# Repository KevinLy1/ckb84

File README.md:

# CKB84
A DIY custom keyboard with 84 keys with per-key rgb and hotswappable keys.
Raspberry Pi RP2040 MCU.

## Features
- Hotswappable
- Per-key RGB Backlight
- 75% Layout
- QMK and Vial support
- 3D printed / CNC case and plate
- Custom layout : Backspace 2u, Left Shift 2u, Right Shift 2u, ISO Enter, Spacebar 6u

# Images

## Layout

## PCB

## Case and Plate

## Firmware

See [QMK Reproducible](https://github.com/KevinLy1/qmk_reproducible) -> diy/ckb84.

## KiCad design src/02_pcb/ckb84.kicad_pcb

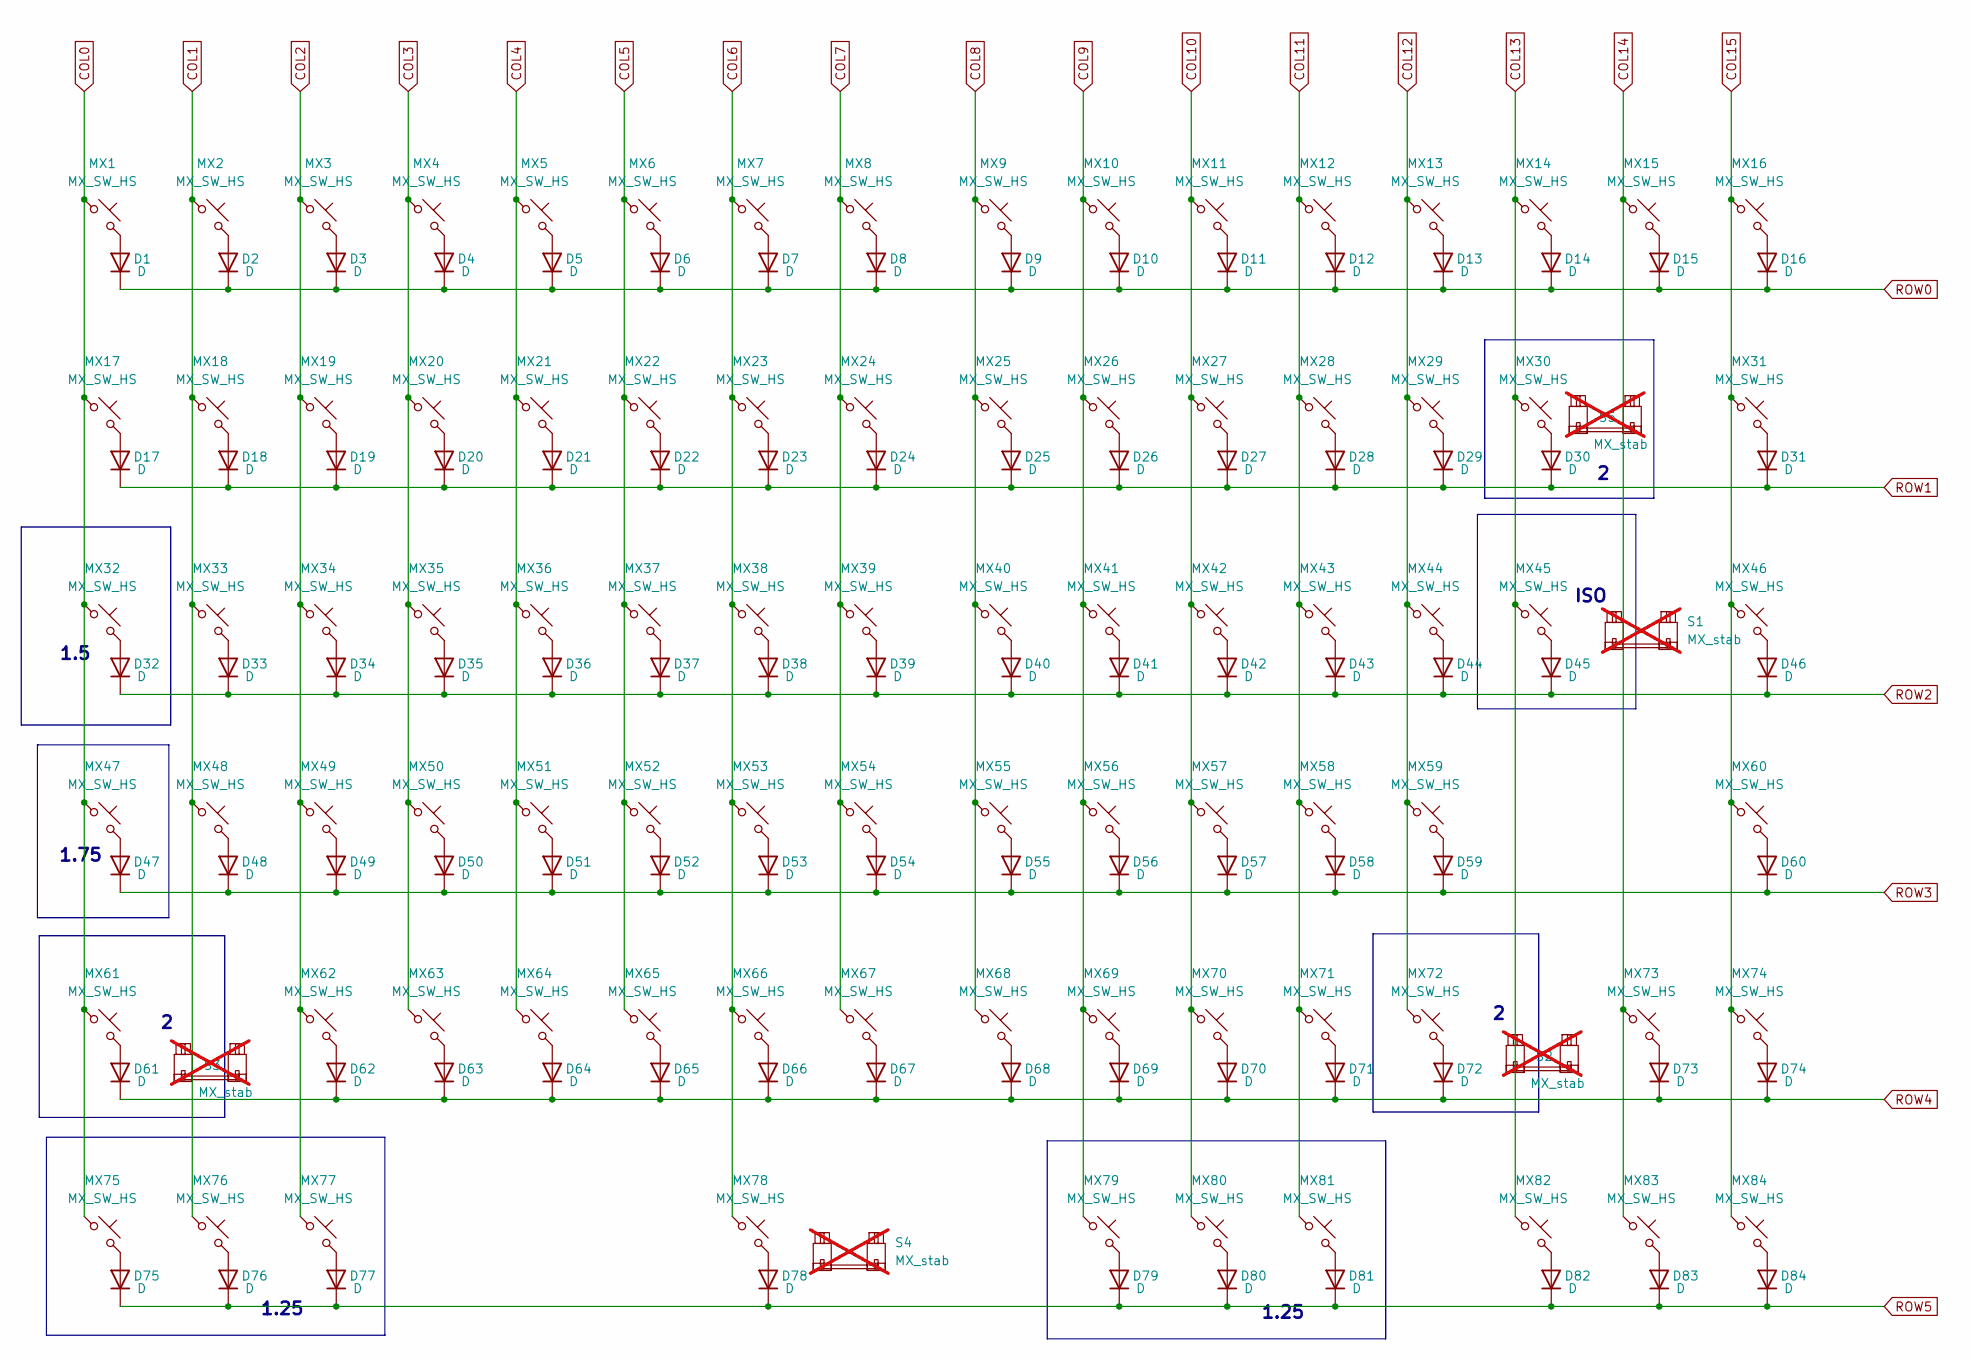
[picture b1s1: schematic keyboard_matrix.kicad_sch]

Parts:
D1, D2, D3, D4, D5, D6, D7, D8, D9, D10, D11, D12, D13, D14, D15, D16, D17, D18, D19, D20, D21, D22, D23, D24, D25, D26, D27, D28, D29, D30, D31, D32, D33, D34, D35, D36, D37, D38, D39, D40, D41, D42, D43, D44, D45, D46, D47, D48, D49, D50, D51, D52, D53, D54, D55, D56, D57, D58, D59, D60, D61, D62, D63, D64, D65, D66, D67, D68, D69, D70, D71, D72, D73, D74, D75, D76, D77, D78, D79, D80, D81, D82, D83, D84: D; D_SOD-123; MFR.Part # SOD1F7; LCSC C33221
MX1, MX2, MX3, MX4, MX5, MX6, MX7, MX8, MX9, MX10, MX11, MX12, MX13, MX14, MX15, MX16, MX17, MX18, MX19, MX20, MX21, MX22, MX23, MX24, MX25, MX26, MX27, MX28, MX29, MX30, MX31, MX33, MX34, MX35, MX36, MX37, MX38, MX39, MX40, MX41, MX42, MX43, MX44, MX45, MX46, MX48, MX49, MX50, MX51, MX52, MX53, MX54, MX55, MX56, MX57, MX58, MX59, MX60, MX61, MX62, MX63, MX64, MX65, MX66, MX67, MX68, MX69, MX70, MX71, MX72, MX73, MX74, MX76, MX78, MX80, MX82, MX83, MX84: MX_SW_HS; SW_MX_HS_CPG151101S11_1u; MFR.Part # CPG151101S11-16; LCSC C41430893
MX32: MX_SW_HS; SW_MX_HS_CPG151101S11_1.5u; MFR.Part # CPG151101S11-16; LCSC C41430893
MX47: MX_SW_HS; SW_MX_HS_CPG151101S11_1.75u; MFR.Part # CPG151101S11-16; LCSC C41430893
MX75, MX77, MX79, MX81: MX_SW_HS; SW_MX_HS_CPG151101S11_1.25u; MFR.Part # CPG151101S11-16; LCSC C41430893
S1: MX_stab; STAB_MX_ISO; MFR.Part # DNP; JLCPCB part# DNP; not fitted
S2, S3, S5: MX_stab; STAB_MX_P_2u; MFR.Part # DNP; JLCPCB part# DNP; not fitted
S4: MX_stab; STAB_MX_6u; MFR.Part # DNP; JLCPCB part# DNP; not fitted

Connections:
COL0: MX1.1, MX17.1, MX32.1, MX47.1, MX61.1, MX75.1; also elsewhere on the board
COL1: MX2.1, MX18.1, MX33.1, MX48.1, MX76.1; also elsewhere on the board
COL2: MX3.1, MX19.1, MX34.1, MX49.1, MX62.1, MX77.1; also elsewhere on the board
COL3: MX4.1, MX20.1, MX35.1, MX50.1, MX63.1; also elsewhere on the board
COL4: MX5.1, MX21.1, MX36.1, MX51.1, MX64.1; also elsewhere on the board
COL5: MX6.1, MX22.1, MX37.1, MX52.1, MX65.1; also elsewhere on the board
COL6: MX7.1, MX23.1, MX38.1, MX53.1, MX66.1, MX78.1; also elsewhere on the board
COL7: MX8.1, MX24.1, MX39.1, MX54.1, MX67.1; also elsewhere on the board
COL8: MX9.1, MX25.1, MX40.1, MX55.1, MX68.1; also elsewhere on the board
COL9: MX10.1, MX26.1, MX41.1, MX56.1, MX69.1, MX79.1; also elsewhere on the board
COL10: MX11.1, MX27.1, MX42.1, MX57.1, MX70.1, MX80.1; also elsewhere on the board
COL11: MX12.1, MX28.1, MX43.1, MX58.1, MX71.1, MX81.1; also elsewhere on the board
COL12: MX13.1, MX29.1, MX44.1, MX59.1, MX72.1; also elsewhere on the board
COL13: MX14.1, MX30.1, MX45.1, MX82.1; also elsewhere on the board
COL14: MX15.1, MX73.1, MX83.1; also elsewhere on the board
COL15: MX16.1, MX31.1, MX46.1, MX60.1, MX74.1, MX84.1; also elsewhere on the board
unnamed: D1.2 (A), MX1.2
unnamed: D2.2 (A), MX2.2
unnamed: D3.2 (A), MX3.2
unnamed: D4.2 (A), MX4.2
unnamed: D5.2 (A), MX5.2
unnamed: D6.2 (A), MX6.2
unnamed: D7.2 (A), MX7.2
unnamed: D8.2 (A), MX8.2
unnamed: D9.2 (A), MX9.2
unnamed: D10.2 (A), MX10.2
unnamed: D11.2 (A), MX11.2
unnamed: D12.2 (A), MX12.2
unnamed: D13.2 (A), MX13.2
unnamed: D14.2 (A), MX14.2
unnamed: D15.2 (A), MX15.2
unnamed: D16.2 (A), MX16.2
unnamed: D17.2 (A), MX17.2
unnamed: D18.2 (A), MX18.2
unnamed: D19.2 (A), MX19.2
unnamed: D20.2 (A), MX20.2
unnamed: D21.2 (A), MX21.2
unnamed: D22.2 (A), MX22.2
unnamed: D23.2 (A), MX23.2
unnamed: D24.2 (A), MX24.2
unnamed: D25.2 (A), MX25.2
unnamed: D26.2 (A), MX26.2
unnamed: D27.2 (A), MX27.2
unnamed: D28.2 (A), MX28.2
unnamed: D29.2 (A), MX29.2
unnamed: D30.2 (A), MX30.2
unnamed: D31.2 (A), MX31.2
unnamed: D32.2 (A), MX32.2
unnamed: D33.2 (A), MX33.2
unnamed: D34.2 (A), MX34.2
unnamed: D35.2 (A), MX35.2
unnamed: D36.2 (A), MX36.2
unnamed: D37.2 (A), MX37.2
unnamed: D38.2 (A), MX38.2
unnamed: D39.2 (A), MX39.2
unnamed: D40.2 (A), MX40.2
unnamed: D41.2 (A), MX41.2
unnamed: D42.2 (A), MX42.2
unnamed: D43.2 (A), MX43.2
unnamed: D44.2 (A), MX44.2
unnamed: D45.2 (A), MX45.2
unnamed: D46.2 (A), MX46.2
unnamed: D47.2 (A), MX47.2
unnamed: D48.2 (A), MX48.2
unnamed: D49.2 (A), MX49.2
unnamed: D50.2 (A), MX50.2
unnamed: D51.2 (A), MX51.2
unnamed: D52.2 (A), MX52.2
unnamed: D53.2 (A), MX53.2
unnamed: D54.2 (A), MX54.2
unnamed: D55.2 (A), MX55.2
unnamed: D56.2 (A), MX56.2
unnamed: D57.2 (A), MX57.2
unnamed: D58.2 (A), MX58.2
unnamed: D59.2 (A), MX59.2
unnamed: D60.2 (A), MX60.2
unnamed: D61.2 (A), MX61.2
unnamed: D62.2 (A), MX62.2
unnamed: D63.2 (A), MX63.2
unnamed: D64.2 (A), MX64.2
unnamed: D65.2 (A), MX65.2
unnamed: D66.2 (A), MX66.2
unnamed: D67.2 (A), MX67.2
unnamed: D68.2 (A), MX68.2
unnamed: D69.2 (A), MX69.2
unnamed: D70.2 (A), MX70.2
unnamed: D71.2 (A), MX71.2
unnamed: D72.2 (A), MX72.2
unnamed: D73.2 (A), MX73.2
unnamed: D74.2 (A), MX74.2
unnamed: D75.2 (A), MX75.2
unnamed: D76.2 (A), MX76.2
unnamed: D77.2 (A), MX77.2
unnamed: D78.2 (A), MX78.2
unnamed: D79.2 (A), MX79.2
unnamed: D80.2 (A), MX80.2
unnamed: D81.2 (A), MX81.2
unnamed: D82.2 (A), MX82.2
unnamed: D83.2 (A), MX83.2
unnamed: D84.2 (A), MX84.2
ROW0: D1.1 (K), D2.1 (K), D3.1 (K), D4.1 (K), D5.1 (K), D6.1 (K), D7.1 (K), D8.1 (K), D9.1 (K), D10.1 (K), D11.1 (K), D12.1 (K), D13.1 (K), D14.1 (K), D15.1 (K), D16.1 (K); also elsewhere on the board
ROW1: D17.1 (K), D18.1 (K), D19.1 (K), D20.1 (K), D21.1 (K), D22.1 (K), D23.1 (K), D24.1 (K), D25.1 (K), D26.1 (K), D27.1 (K), D28.1 (K), D29.1 (K), D30.1 (K), D31.1 (K); also elsewhere on the board
ROW2: D32.1 (K), D33.1 (K), D34.1 (K), D35.1 (K), D36.1 (K), D37.1 (K), D38.1 (K), D39.1 (K), D40.1 (K), D41.1 (K), D42.1 (K), D43.1 (K), D44.1 (K), D45.1 (K), D46.1 (K); also elsewhere on the board
ROW3: D47.1 (K), D48.1 (K), D49.1 (K), D50.1 (K), D51.1 (K), D52.1 (K), D53.1 (K), D54.1 (K), D55.1 (K), D56.1 (K), D57.1 (K), D58.1 (K), D59.1 (K), D60.1 (K); also elsewhere on the board
ROW4: D61.1 (K), D62.1 (K), D63.1 (K), D64.1 (K), D65.1 (K), D66.1 (K), D67.1 (K), D68.1 (K), D69.1 (K), D70.1 (K), D71.1 (K), D72.1 (K), D73.1 (K), D74.1 (K); also elsewhere on the board
ROW5: D75.1 (K), D76.1 (K), D77.1 (K), D78.1 (K), D79.1 (K), D80.1 (K), D81.1 (K), D82.1 (K), D83.1 (K), D84.1 (K); also elsewhere on the board

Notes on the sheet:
ISO
1.75
1.25
1.5

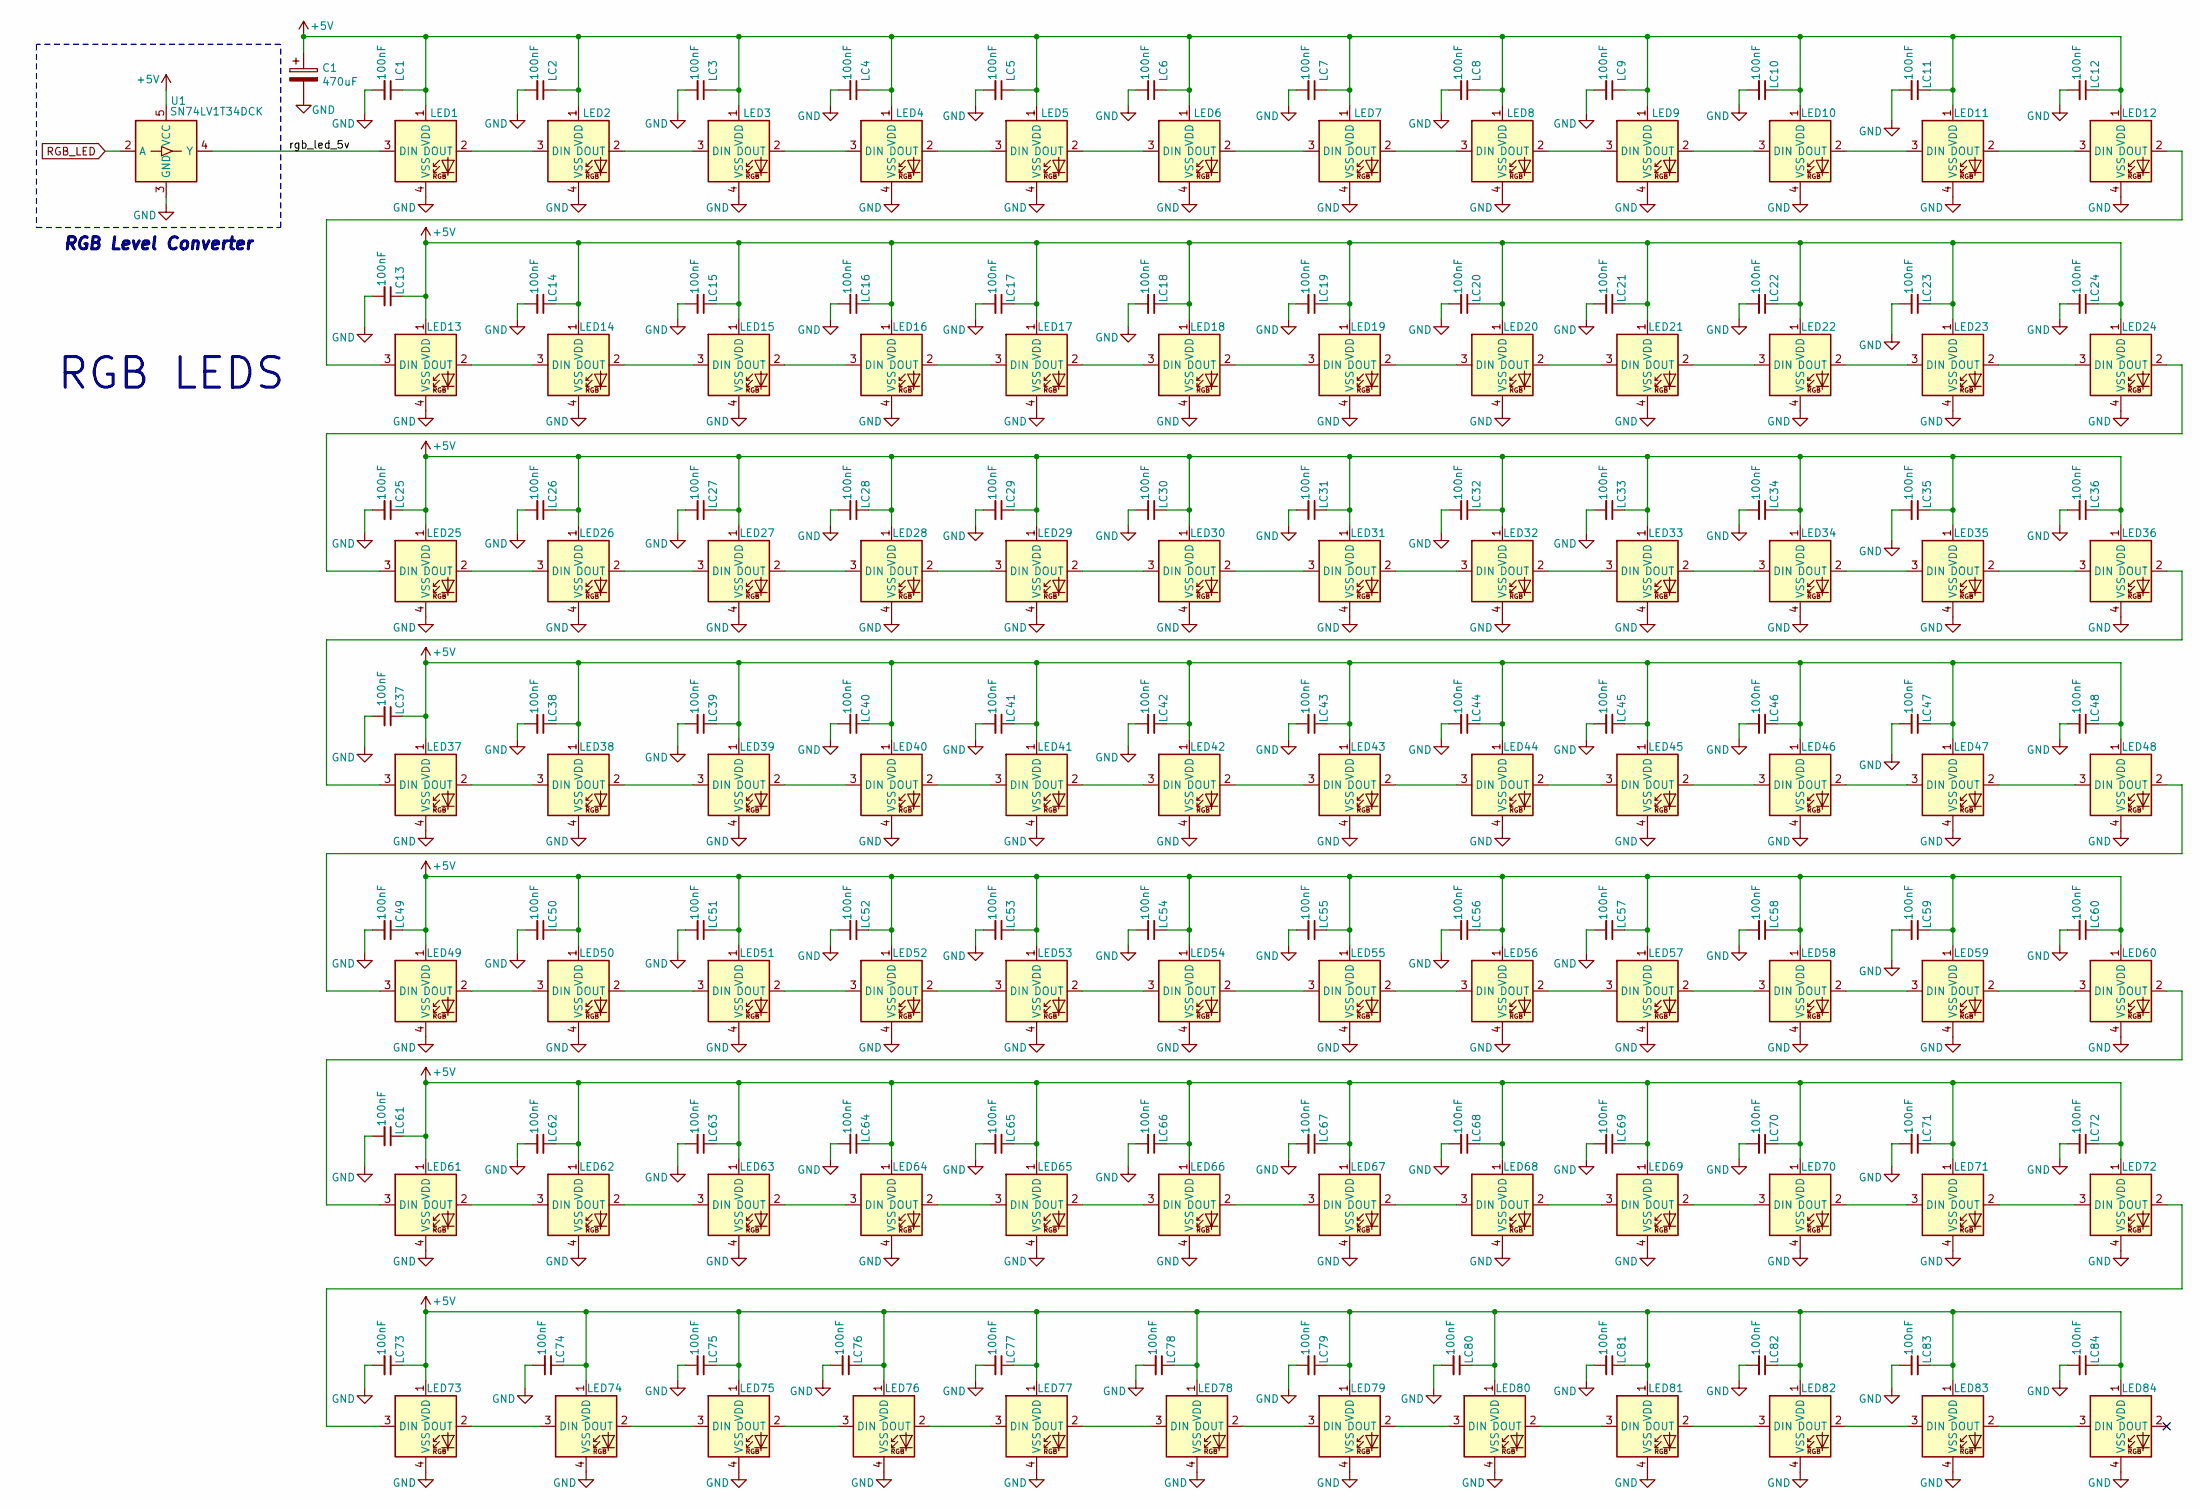
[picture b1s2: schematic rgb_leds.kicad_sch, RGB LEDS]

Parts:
C1: 470uF; CP_EIA-7343-31_Kemet-D; MFR.Part # TAJD477K006RNJ; JLCPCB Part # C7229
LC1, LC2, LC3, LC4, LC5, LC6, LC7, LC8, LC9, LC10, LC11, LC12, LC13, LC14, LC15, LC16, LC17, LC18, LC19, LC20, LC21, LC22, LC23, LC24, LC25, LC26, LC27, LC28, LC29, LC30, LC31, LC32, LC33, LC34, LC35, LC36, LC37, LC38, LC39, LC40, LC41, LC42, LC43, LC44, LC45, LC46, LC47, LC48, LC49, LC50, LC51, LC52, LC53, LC54, LC55, LC56, LC57, LC58, LC59, LC60, LC61, LC62, LC63, LC64, LC65, LC66, LC67, LC68, LC69, LC70, LC71, LC72, LC73, LC74, LC75, LC76, LC77, LC78, LC79, LC80, LC81, LC82, LC83, LC84: 100nF; C_0402_1005Metric; LCSC C1525
LED1, LED2, LED3, LED4, LED5, LED6, LED7, LED8, LED9, LED10, LED11, LED12, LED13, LED14, LED15, LED16, LED17, LED18, LED19, LED20, LED21, LED22, LED23, LED24, LED25, LED26, LED27, LED28, LED29, LED30, LED31, LED32, LED33, LED34, LED35, LED36, LED37, LED38, LED39, LED40, LED41, LED42, LED43, LED44, LED45, LED46, LED47, LED48, LED49, LED50, LED51, LED52, LED53, LED54, LED55, LED56, LED57, LED58, LED59, LED60, LED61, LED62, LED63, LED64, LED65, LED66, LED67, LED68, LED69, LED70, LED71, LED72, LED73, LED74, LED75, LED76, LED77, LED78, LED79, LED80, LED81, LED82, LED83, LED84: MX_SK6812MINI-E; LED_MX_6028R; LCSC C5149201
U1: SN74LV1T34DCK; SOT-353_SC-70-5; LCSC C48543212

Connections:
+5V: C1.1, LC1.1, LC2.1, LC3.1, LC4.1, LC5.1, LC6.1, LC7.1, LC8.1, LC9.1, LC10.1, LC11.1, LC12.1, LC13.1, LC14.1, LC15.1, LC16.1, LC17.1, LC18.1, LC19.1, LC20.1, LC21.1, LC22.1, LC23.1, LC24.1, LC25.1, LC26.1, LC27.1, LC28.1, LC29.1, LC30.1, LC31.1, LC32.1, LC33.1, LC34.1, LC35.1, LC36.1, LC37.1, LC38.1, LC39.1, LC40.1, LC41.1, LC42.1, LC43.1, LC44.1, LC45.1, LC46.1, LC47.1, LC48.1, LC49.1, LC50.1, LC51.1, LC52.1, LC53.1, LC54.1, LC55.1, LC56.1, LC57.1, LC58.1, LC59.1, LC60.1, LC61.1, LC62.1, LC63.1, LC64.1, LC65.1, LC66.1, LC67.1, LC68.1, LC69.1, LC70.1, LC71.1, LC72.1, LC73.1, LC74.1, LC75.1, LC76.1, LC77.1, LC78.1, LC79.1, LC80.1, LC81.1, LC82.1, LC83.1, LC84.1, LED1.1 (VDD), LED2.1 (VDD), LED3.1 (VDD), LED4.1 (VDD), LED5.1 (VDD), LED6.1 (VDD), LED7.1 (VDD), LED8.1 (VDD), LED9.1 (VDD), LED10.1 (VDD), LED11.1 (VDD), LED12.1 (VDD), LED13.1 (VDD), LED14.1 (VDD), LED15.1 (VDD), LED16.1 (VDD), LED17.1 (VDD), LED18.1 (VDD), LED19.1 (VDD), LED20.1 (VDD), LED21.1 (VDD), LED22.1 (VDD), LED23.1 (VDD), LED24.1 (VDD), LED25.1 (VDD), LED26.1 (VDD), LED27.1 (VDD), LED28.1 (VDD), LED29.1 (VDD), LED30.1 (VDD), LED31.1 (VDD), LED32.1 (VDD), LED33.1 (VDD), LED34.1 (VDD), LED35.1 (VDD), LED36.1 (VDD), LED37.1 (VDD), LED38.1 (VDD), LED39.1 (VDD), LED40.1 (VDD), LED41.1 (VDD), LED42.1 (VDD), LED43.1 (VDD), LED44.1 (VDD), LED45.1 (VDD), LED46.1 (VDD), LED47.1 (VDD), LED48.1 (VDD), LED49.1 (VDD), LED50.1 (VDD), LED51.1 (VDD), LED52.1 (VDD), LED53.1 (VDD), LED54.1 (VDD), LED55.1 (VDD), LED56.1 (VDD), LED57.1 (VDD), LED58.1 (VDD), LED59.1 (VDD), LED60.1 (VDD), LED61.1 (VDD), LED62.1 (VDD), LED63.1 (VDD), LED64.1 (VDD), LED65.1 (VDD), LED66.1 (VDD), LED67.1 (VDD), LED68.1 (VDD), LED69.1 (VDD), LED70.1 (VDD), LED71.1 (VDD), LED72.1 (VDD), LED73.1 (VDD), LED74.1 (VDD), LED75.1 (VDD), LED76.1 (VDD), LED77.1 (VDD), LED78.1 (VDD), LED79.1 (VDD), LED80.1 (VDD), LED81.1 (VDD), LED82.1 (VDD), LED83.1 (VDD), LED84.1 (VDD), U1.5 (VCC); also elsewhere on the board
/RGB LEDs/rgb_led_5v: LED1.3 (DIN), U1.4 (Y)
GND: C1.2, LC1.2, LC2.2, LC3.2, LC4.2, LC5.2, LC6.2, LC7.2, LC8.2, LC9.2, LC10.2, LC11.2, LC12.2, LC13.2, LC14.2, LC15.2, LC16.2, LC17.2, LC18.2, LC19.2, LC20.2, LC21.2, LC22.2, LC23.2, LC24.2, LC25.2, LC26.2, LC27.2, LC28.2, LC29.2, LC30.2, LC31.2, LC32.2, LC33.2, LC34.2, LC35.2, LC36.2, LC37.2, LC38.2, LC39.2, LC40.2, LC41.2, LC42.2, LC43.2, LC44.2, LC45.2, LC46.2, LC47.2, LC48.2, LC49.2, LC50.2, LC51.2, LC52.2, LC53.2, LC54.2, LC55.2, LC56.2, LC57.2, LC58.2, LC59.2, LC60.2, LC61.2, LC62.2, LC63.2, LC64.2, LC65.2, LC66.2, LC67.2, LC68.2, LC69.2, LC70.2, LC71.2, LC72.2, LC73.2, LC74.2, LC75.2, LC76.2, LC77.2, LC78.2, LC79.2, LC80.2, LC81.2, LC82.2, LC83.2, LC84.2, LED1.4 (VSS), LED2.4 (VSS), LED3.4 (VSS), LED4.4 (VSS), LED5.4 (VSS), LED6.4 (VSS), LED7.4 (VSS), LED8.4 (VSS), LED9.4 (VSS), LED10.4 (VSS), LED11.4 (VSS), LED12.4 (VSS), LED13.4 (VSS), LED14.4 (VSS), LED15.4 (VSS), LED16.4 (VSS), LED17.4 (VSS), LED18.4 (VSS), LED19.4 (VSS), LED20.4 (VSS), LED21.4 (VSS), LED22.4 (VSS), LED23.4 (VSS), LED24.4 (VSS), LED25.4 (VSS), LED26.4 (VSS), LED27.4 (VSS), LED28.4 (VSS), LED29.4 (VSS), LED30.4 (VSS), LED31.4 (VSS), LED32.4 (VSS), LED33.4 (VSS), LED34.4 (VSS), LED35.4 (VSS), LED36.4 (VSS), LED37.4 (VSS), LED38.4 (VSS), LED39.4 (VSS), LED40.4 (VSS), LED41.4 (VSS), LED42.4 (VSS), LED43.4 (VSS), LED44.4 (VSS), LED45.4 (VSS), LED46.4 (VSS), LED47.4 (VSS), LED48.4 (VSS), LED49.4 (VSS), LED50.4 (VSS), LED51.4 (VSS), LED52.4 (VSS), LED53.4 (VSS), LED54.4 (VSS), LED55.4 (VSS), LED56.4 (VSS), LED57.4 (VSS), LED58.4 (VSS), LED59.4 (VSS), LED60.4 (VSS), LED61.4 (VSS), LED62.4 (VSS), LED63.4 (VSS), LED64.4 (VSS), LED65.4 (VSS), LED66.4 (VSS), LED67.4 (VSS), LED68.4 (VSS), LED69.4 (VSS), LED70.4 (VSS), LED71.4 (VSS), LED72.4 (VSS), LED73.4 (VSS), LED74.4 (VSS), LED75.4 (VSS), LED76.4 (VSS), LED77.4 (VSS), LED78.4 (VSS), LED79.4 (VSS), LED80.4 (VSS), LED81.4 (VSS), LED82.4 (VSS), LED83.4 (VSS), LED84.4 (VSS), U1.3 (GND); also elsewhere on the board
unnamed: LED1.2 (DOUT), LED2.3 (DIN)
unnamed: LED2.2 (DOUT), LED3.3 (DIN)
unnamed: LED3.2 (DOUT), LED4.3 (DIN)
unnamed: LED4.2 (DOUT), LED5.3 (DIN)
unnamed: LED5.2 (DOUT), LED6.3 (DIN)
unnamed: LED6.2 (DOUT), LED7.3 (DIN)
unnamed: LED7.2 (DOUT), LED8.3 (DIN)
unnamed: LED8.2 (DOUT), LED9.3 (DIN)
unnamed: LED9.2 (DOUT), LED10.3 (DIN)
unnamed: LED10.2 (DOUT), LED11.3 (DIN)
unnamed: LED11.2 (DOUT), LED12.3 (DIN)
unnamed: LED12.2 (DOUT), LED13.3 (DIN)
unnamed: LED13.2 (DOUT), LED14.3 (DIN)
unnamed: LED14.2 (DOUT), LED15.3 (DIN)
unnamed: LED15.2 (DOUT), LED16.3 (DIN)
unnamed: LED16.2 (DOUT), LED17.3 (DIN)
unnamed: LED17.2 (DOUT), LED18.3 (DIN)
unnamed: LED18.2 (DOUT), LED19.3 (DIN)
unnamed: LED19.2 (DOUT), LED20.3 (DIN)
unnamed: LED20.2 (DOUT), LED21.3 (DIN)
unnamed: LED21.2 (DOUT), LED22.3 (DIN)
unnamed: LED22.2 (DOUT), LED23.3 (DIN)
unnamed: LED23.2 (DOUT), LED24.3 (DIN)
unnamed: LED24.2 (DOUT), LED25.3 (DIN)
unnamed: LED25.2 (DOUT), LED26.3 (DIN)
unnamed: LED26.2 (DOUT), LED27.3 (DIN)
unnamed: LED27.2 (DOUT), LED28.3 (DIN)
unnamed: LED28.2 (DOUT), LED29.3 (DIN)
unnamed: LED29.2 (DOUT), LED30.3 (DIN)
unnamed: LED30.2 (DOUT), LED31.3 (DIN)
unnamed: LED31.2 (DOUT), LED32.3 (DIN)
unnamed: LED32.2 (DOUT), LED33.3 (DIN)
unnamed: LED33.2 (DOUT), LED34.3 (DIN)
unnamed: LED34.2 (DOUT), LED35.3 (DIN)
unnamed: LED35.2 (DOUT), LED36.3 (DIN)
unnamed: LED36.2 (DOUT), LED37.3 (DIN)
unnamed: LED37.2 (DOUT), LED38.3 (DIN)
unnamed: LED38.2 (DOUT), LED39.3 (DIN)
unnamed: LED39.2 (DOUT), LED40.3 (DIN)
unnamed: LED40.2 (DOUT), LED41.3 (DIN)
unnamed: LED41.2 (DOUT), LED42.3 (DIN)
unnamed: LED42.2 (DOUT), LED43.3 (DIN)
unnamed: LED43.2 (DOUT), LED44.3 (DIN)
unnamed: LED44.2 (DOUT), LED45.3 (DIN)
unnamed: LED45.2 (DOUT), LED46.3 (DIN)
unnamed: LED46.2 (DOUT), LED47.3 (DIN)
unnamed: LED47.2 (DOUT), LED48.3 (DIN)
unnamed: LED48.2 (DOUT), LED49.3 (DIN)
unnamed: LED49.2 (DOUT), LED50.3 (DIN)
unnamed: LED50.2 (DOUT), LED51.3 (DIN)
unnamed: LED51.2 (DOUT), LED52.3 (DIN)
unnamed: LED52.2 (DOUT), LED53.3 (DIN)
unnamed: LED53.2 (DOUT), LED54.3 (DIN)
unnamed: LED54.2 (DOUT), LED55.3 (DIN)
unnamed: LED55.2 (DOUT), LED56.3 (DIN)
unnamed: LED56.2 (DOUT), LED57.3 (DIN)
unnamed: LED57.2 (DOUT), LED58.3 (DIN)
unnamed: LED58.2 (DOUT), LED59.3 (DIN)
unnamed: LED59.2 (DOUT), LED60.3 (DIN)
unnamed: LED60.2 (DOUT), LED61.3 (DIN)
unnamed: LED61.2 (DOUT), LED62.3 (DIN)
unnamed: LED62.2 (DOUT), LED63.3 (DIN)
unnamed: LED63.2 (DOUT), LED64.3 (DIN)
unnamed: LED64.2 (DOUT), LED65.3 (DIN)
unnamed: LED65.2 (DOUT), LED66.3 (DIN)
unnamed: LED66.2 (DOUT), LED67.3 (DIN)
unnamed: LED67.2 (DOUT), LED68.3 (DIN)
unnamed: LED68.2 (DOUT), LED69.3 (DIN)
unnamed: LED69.2 (DOUT), LED70.3 (DIN)
unnamed: LED70.2 (DOUT), LED71.3 (DIN)
unnamed: LED71.2 (DOUT), LED72.3 (DIN)
unnamed: LED72.2 (DOUT), LED73.3 (DIN)
unnamed: LED73.2 (DOUT), LED74.3 (DIN)
unnamed: LED74.2 (DOUT), LED75.3 (DIN)
unnamed: LED75.2 (DOUT), LED76.3 (DIN)
unnamed: LED76.2 (DOUT), LED77.3 (DIN)
unnamed: LED77.2 (DOUT), LED78.3 (DIN)
unnamed: LED78.2 (DOUT), LED79.3 (DIN)
unnamed: LED79.2 (DOUT), LED80.3 (DIN)
unnamed: LED80.2 (DOUT), LED81.3 (DIN)
unnamed: LED81.2 (DOUT), LED82.3 (DIN)
unnamed: LED82.2 (DOUT), LED83.3 (DIN)
unnamed: LED83.2 (DOUT), LED84.3 (DIN)
RGB_LED: U1.2 (A); also elsewhere on the board

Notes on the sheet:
RGB Level Converter
RGB LEDS

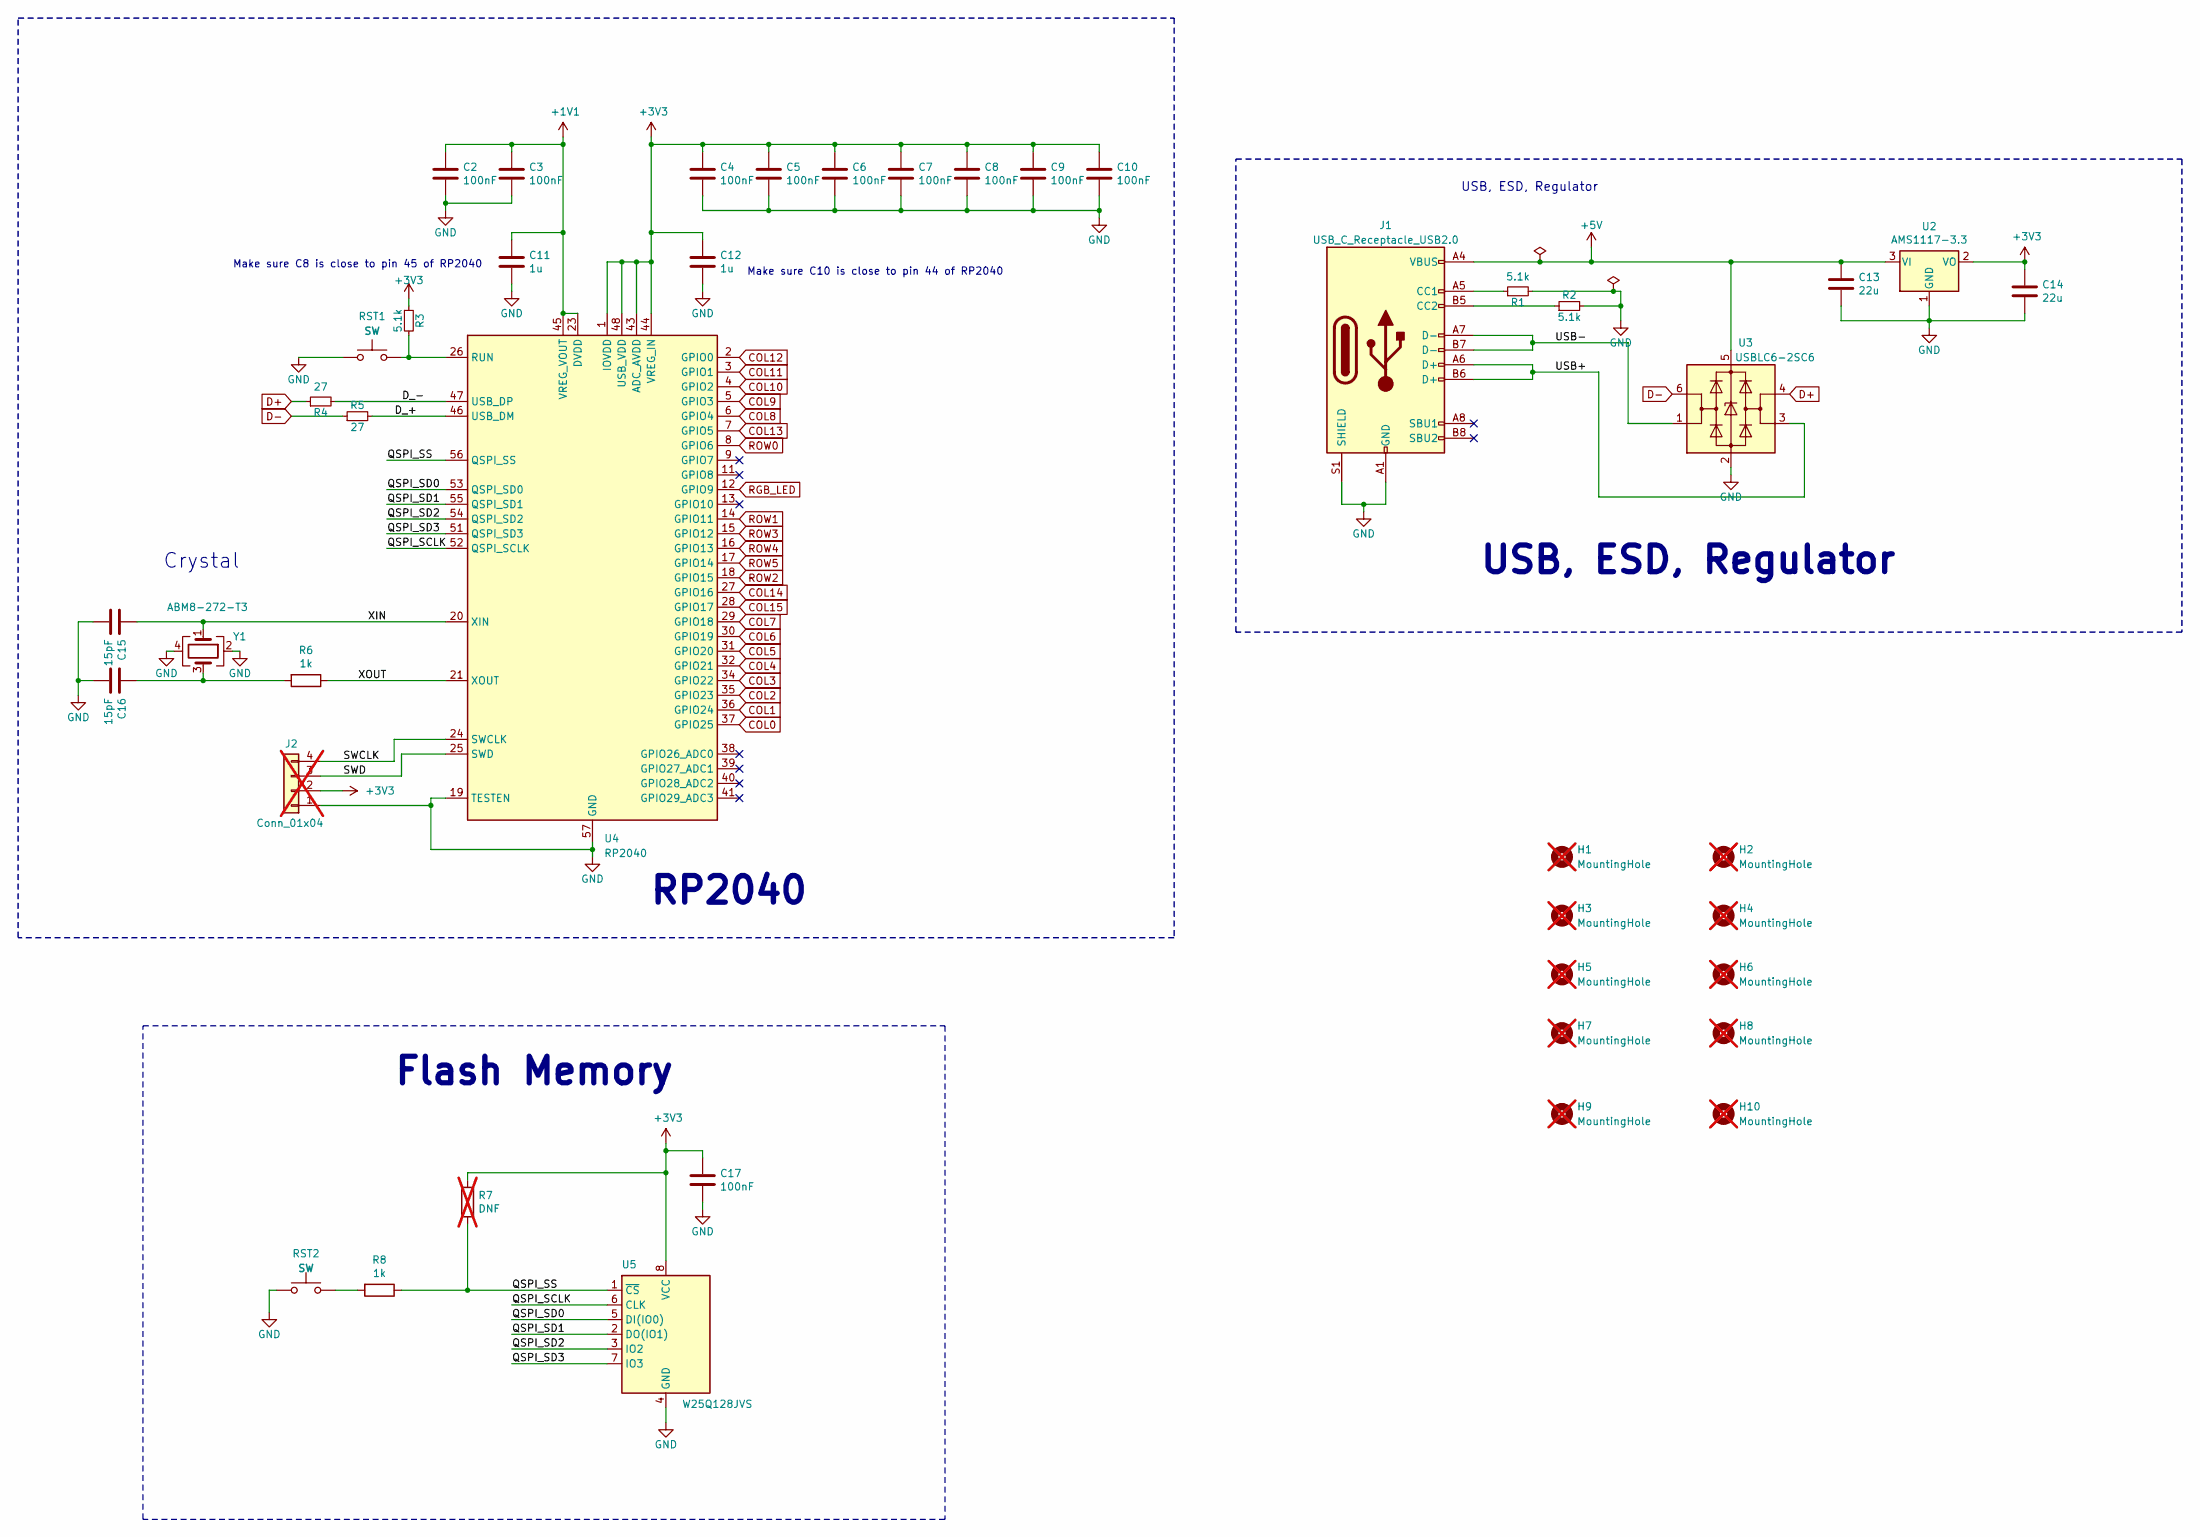
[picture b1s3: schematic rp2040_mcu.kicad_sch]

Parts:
C2, C3, C4, C5, C6, C7, C8, C9, C10, C17: 100nF; C_0402_1005Metric; MFR.Part # CL05B104KO5NNNC; LCSC C1525
C11, C12: 1u; C_0402_1005Metric; MFR.Part # CL05A105KA5NQNC; LCSC C52923
C13, C14: 22u; C_0603_1608Metric; MFR.Part # CL10A226MQ8NRNC; LCSC C59461
C15, C16: 15pF; C_0402_1005Metric; MFR.Part # 0402CG150J500NT; LCSC C1548
H1, H2, H3, H4, H5, H6, H7, H8, H9, H10: MountingHole; MountingHole_2.2mm_M2; not fitted
J1: USB_C_Receptacle_USB2.0; USB_C_Receptacle_HRO_TYPE-C-31-M-12; LCSC C165948
J2: Conn_01x04; PinHeader_1x04_P2.00mm_Vertical; MFR.Part # DNP; JLCPCB part# DNP; not fitted
R1, R2: 5.1k; R_0402_1005Metric_Pad0.72x0.64mm_HandSolder; LCSC C25905
R3: 5.1k; R_0402_1005Metric_Pad0.72x0.64mm_HandSolder; MFR.Part # 0402WGF5101TCE; LCSC C25905
R4, R5: 27; R_0402_1005Metric_Pad0.72x0.64mm_HandSolder; MFR.Part # 0402WGF270JTCE; LCSC C226392
R6: 1k; R_0402_1005Metric; MFR.Part # 0402WGF1001TCE; LCSC C11702
R7: DNF; R_0402_1005Metric; MFR.Part # DNP; JLCPCB part# DNP; not fitted
R8: 1k; R_0402_1005Metric; LCSC C11702
RST1: SW; SW_SPST_SKQG_WithStem; MFR.Part # TS5215A 250gf 025; LCSC C5140332
RST2: SW; SW_SPST_SKQG_WithStem; MFR.Part # TS5215A 250gf 025; JLC C5140332
U2: AMS1117-3.3; SOT-223-3_TabPin2; MFR.Part # AMS1117-3.3; LCSC C6186
U3: USBLC6-2SC6; SOT-23-6; MFR.Part # USBLC6-2SC6; LCSC C558442
U4: RP2040; QFN-56-1EP_7x7mm_P0.4mm_EP3.2x3.2mm; MFR.Part # RP2040; LCSC C2040
U5: W25Q128JVS; SOIC127P790X216-8N; MFR.Part # W25Q128JVSIQ; LCSC C97521
Y1: ABM8-272-T3; Crystal_SMD_3225-4Pin_3.2x2.5mm; MFR.Part # ABM8-272-T3; LCSC C20625731

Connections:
+1V1: C2.1, C3.1, C11.1, U4.23 (DVDD), U4.45 (VREG_VOUT), U4.50 (DVDD)
+3V3: C4.1, C5.1, C6.1, C7.1, C8.1, C9.1, C10.1, C12.1, C14.1, C17.1, J2.2, R3.1, R7.1, U2.2 (VO), U4.1 (IOVDD), U4.10 (IOVDD), U4.22 (IOVDD), U4.33 (IOVDD), U4.42 (IOVDD), U4.43 (ADC_AVDD), U4.44 (VREG_IN), U4.48 (USB_VDD), U4.49 (IOVDD), U5.8 (VCC)
+5V: C13.1, J1.A4 (VBUS), J1.A9 (VBUS), J1.B4 (VBUS), J1.B9 (VBUS), U2.3 (VI), U3.5 (VBUS); also elsewhere on the board
/RP2040 MCU/D_+: R5.2, U4.46 (USB_DM)
/RP2040 MCU/D_-: R4.2, U4.47 (USB_DP)
/RP2040 MCU/QSPI_SCLK: U4.52 (QSPI_SCLK), U5.6 (CLK)
/RP2040 MCU/QSPI_SD0: U4.53 (QSPI_SD0), U5.5 (DI(IO0))
/RP2040 MCU/QSPI_SD1: U4.55 (QSPI_SD1), U5.2 (DO(IO1))
/RP2040 MCU/QSPI_SD2: U4.54 (QSPI_SD2), U5.3 (IO2)
/RP2040 MCU/QSPI_SD3: U4.51 (QSPI_SD3), U5.7 (IO3)
/RP2040 MCU/QSPI_SS: R7.2, R8.1, U4.56 (QSPI_SS), U5.1 (~CS)
/RP2040 MCU/SWCLK: J2.4, U4.24 (SWCLK)
/RP2040 MCU/SWD: J2.3, U4.25 (SWD)
/RP2040 MCU/USB+: J1.A6 (D+), J1.B6 (D+), U3.3 (I/O2)
/RP2040 MCU/USB-: J1.A7 (D-), J1.B7 (D-), U3.1 (I/O1)
/RP2040 MCU/XIN: C15.1, U4.20 (XIN), Y1.1
/RP2040 MCU/XOUT: R6.1, U4.21 (XOUT)
COL0: U4.37 (GPIO25); also elsewhere on the board
COL1: U4.36 (GPIO24); also elsewhere on the board
COL2: U4.35 (GPIO23); also elsewhere on the board
COL3: U4.34 (GPIO22); also elsewhere on the board
COL4: U4.32 (GPIO21); also elsewhere on the board
COL5: U4.31 (GPIO20); also elsewhere on the board
COL6: U4.30 (GPIO19); also elsewhere on the board
COL7: U4.29 (GPIO18); also elsewhere on the board
COL8: U4.6 (GPIO4); also elsewhere on the board
COL9: U4.5 (GPIO3); also elsewhere on the board
COL10: U4.4 (GPIO2); also elsewhere on the board
COL11: U4.3 (GPIO1); also elsewhere on the board
COL12: U4.2 (GPIO0); also elsewhere on the board
COL13: U4.7 (GPIO5); also elsewhere on the board
COL14: U4.27 (GPIO16); also elsewhere on the board
COL15: U4.28 (GPIO17); also elsewhere on the board
D+: R4.1, U3.4 (I/O2)
D-: R5.1, U3.6 (I/O1)
GND: C2.2, C3.2, C4.2, C5.2, C6.2, C7.2, C8.2, C9.2, C10.2, C11.2, C12.2, C13.2, C14.2, C15.2, C16.2, C17.2, J1.A1 (GND), J1.A12 (GND), J1.B1 (GND), J1.B12 (GND), J1.S1 (SHIELD), J2.1, R1.2, R2.2, RST1.1, RST2.2, U2.1 (GND), U3.2 (GND), U4.19 (TESTEN), U4.57 (GND), U5.4 (GND), Y1.2, Y1.4; also elsewhere on the board
unnamed: C16.1, R6.2, Y1.3
unnamed: J1.A5 (CC1), R1.1
unnamed: J1.B5 (CC2), R2.1
unnamed: R8.2, RST2.1
unnamed: R3.2, RST1.2, U4.26 (RUN)
RGB_LED: U4.12 (GPIO9); also elsewhere on the board
ROW0: U4.8 (GPIO6); also elsewhere on the board
ROW1: U4.14 (GPIO11); also elsewhere on the board
ROW2: U4.18 (GPIO15); also elsewhere on the board
ROW3: U4.15 (GPIO12); also elsewhere on the board
ROW4: U4.16 (GPIO13); also elsewhere on the board
ROW5: U4.17 (GPIO14); also elsewhere on the board

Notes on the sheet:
USB, ESD, Regulator
Flash Memory
Make sure C10 is close to pin 44 of RP2040
Crystal
RP2040
Make sure C8 is close to pin 45 of RP2040

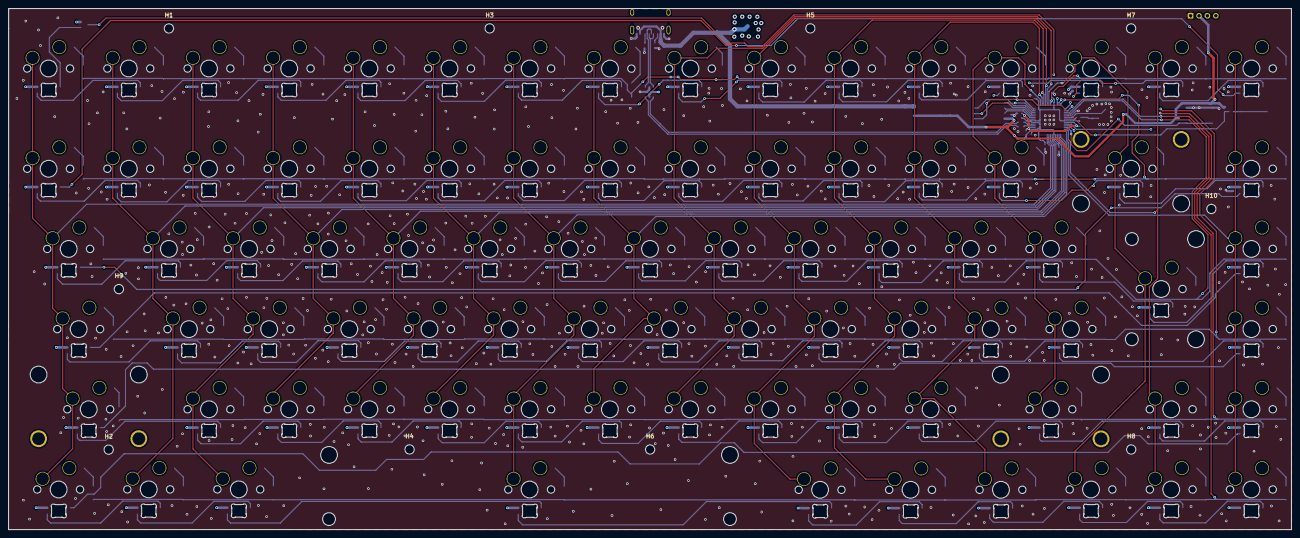
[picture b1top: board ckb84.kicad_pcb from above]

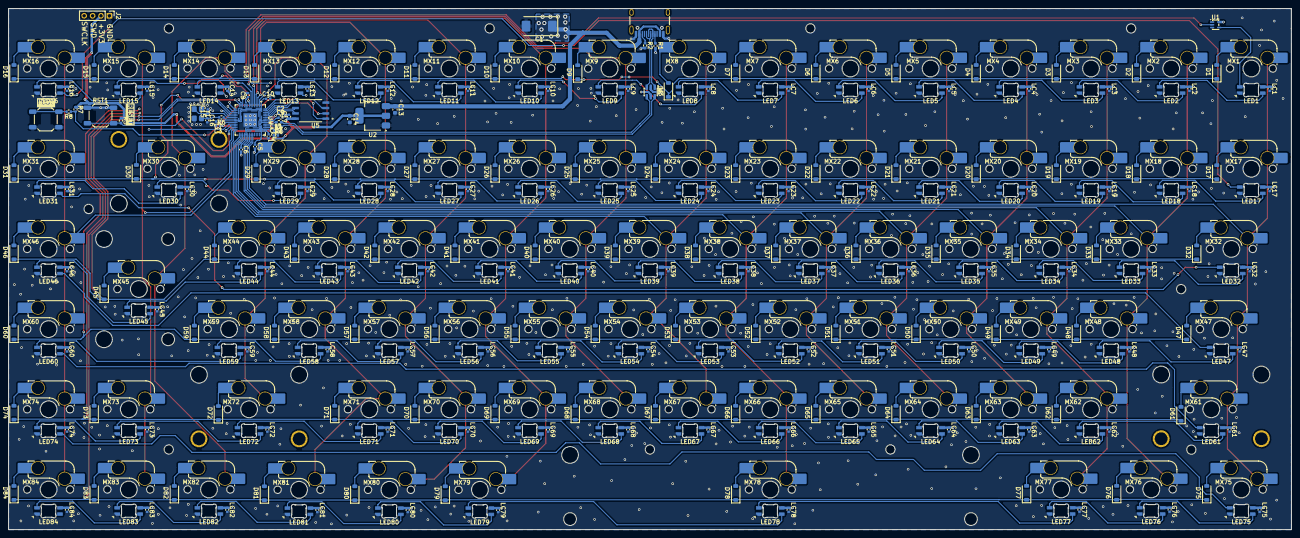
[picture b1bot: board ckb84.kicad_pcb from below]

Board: 4 copper layers, 304.8 x 123.8 mm, 388 parts (377 on the bottom side), 216 nets.

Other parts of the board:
kibuzzard-6A6FB6DB: G***; kibuzzard-6A6FB6DB
kibuzzard-6A6FB680: G***; kibuzzard-6A6FB680
